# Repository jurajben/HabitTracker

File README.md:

# HabitTracker

A handheld habit tracking device with reminders, built with Arduino Nano, OLED display and RTC module.

## Hardware
- MCU: Arduino Nano (ATmega328P)
- Display: SSD1306 128×64 I2C
- RTC: DS3231 (ZS-042)
- Input: 5D Joystick module (7 buttons)
- Buzzer: KY-006
- Power: TP4056 + MT3608 boost converter

## Schematic

## Firmware
Arduino (C++)

### Build
Open `Habit_Tracker/Habit_Tracker.ino` in Arduino IDE and upload to Arduino Nano.

## License
- Firmware: [MIT](LICENSE)
- Hardware: [CERN OHL-S v2](LICENSE.hardware)

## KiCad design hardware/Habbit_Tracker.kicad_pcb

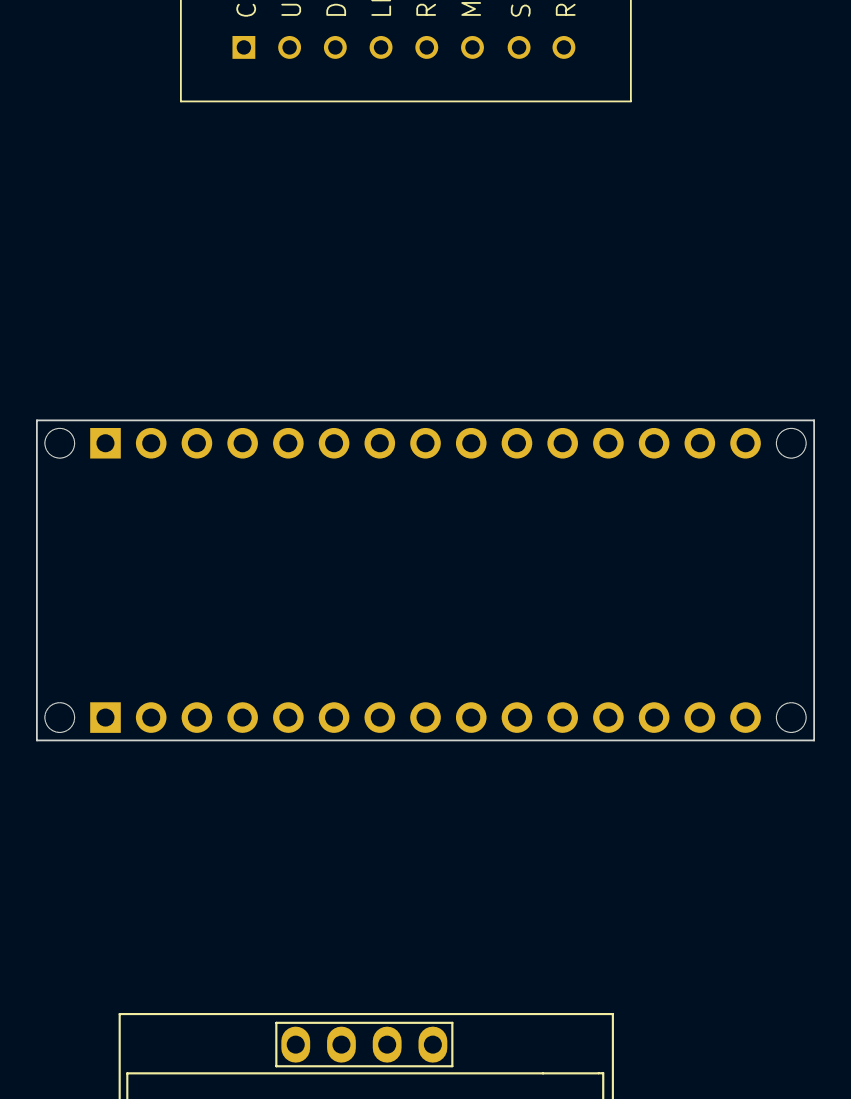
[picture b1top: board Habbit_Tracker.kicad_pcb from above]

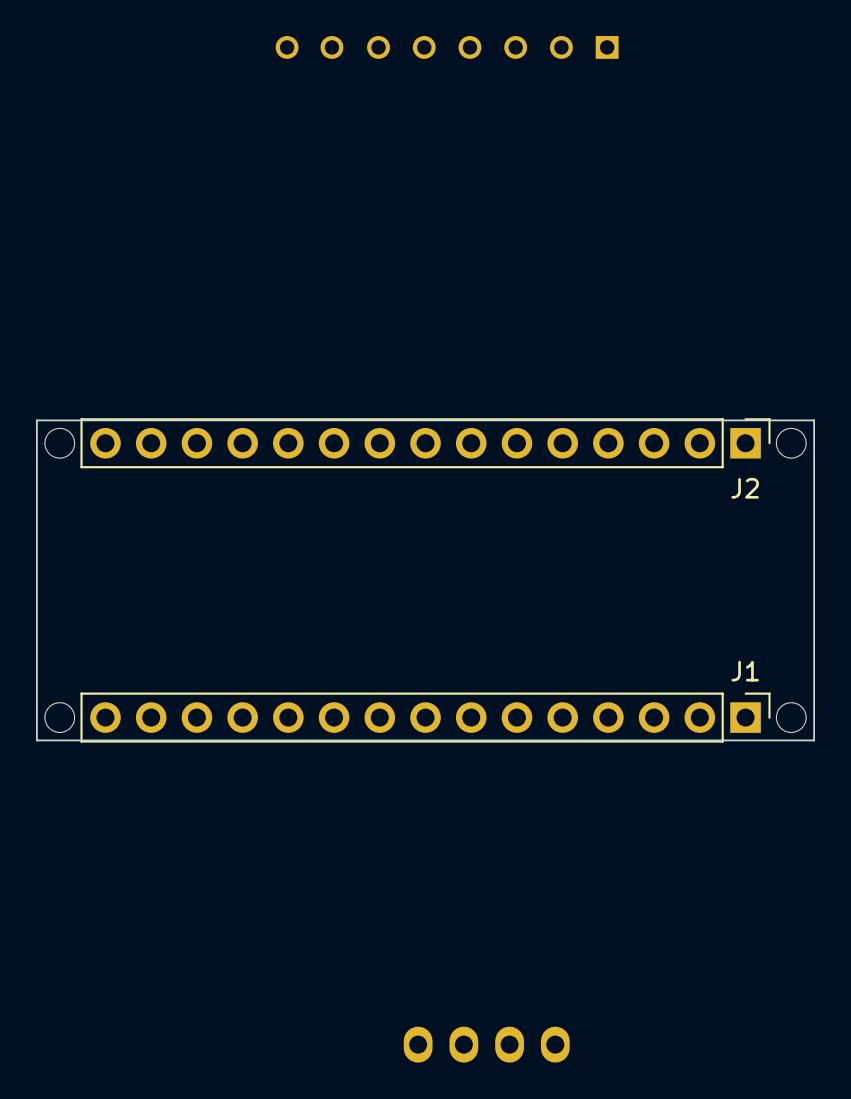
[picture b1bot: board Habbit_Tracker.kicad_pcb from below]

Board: 2 copper layers, 43.2 x 17.8 mm, 8 parts (2 on the bottom side), 12 nets, no tracks yet.

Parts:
Brd1: SSD1306; 128x64OLED
J1: Analog; PinHeader_1x15_P2.54mm_Vertical
J2: Digital; PinHeader_1x15_P2.54mm_Vertical
MH1, MH2, MH3, MH4: MountingHole_65mil
U1: 5D-Joystick; Untitled

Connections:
+3V3: Brd1.2 (VCC), J1.2
/*D3: J2.10, U1.7 (SET)
/*D5: J2.8, U1.5 (RHT)
/*D6: J2.7, U1.4 (LFT)
/A4/SDA: Brd1.4 (SDA), J1.8
/A5/SCL: Brd1.3 (SCL), J1.9
/D2: J2.11, U1.8 (RST)
/D4: J2.9, U1.6 (MID)
/D7: J2.6, U1.3 (DWN)
/D8: J2.5, U1.2 (UP)
/~RESET: J1.13, J2.13
GND: Brd1.1 (GND), J1.14, J2.12, U1.1 (COM)
